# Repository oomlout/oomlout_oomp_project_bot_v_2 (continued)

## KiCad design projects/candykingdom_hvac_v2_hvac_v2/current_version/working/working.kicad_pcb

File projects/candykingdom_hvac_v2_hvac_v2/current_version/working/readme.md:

# hvac_v2
 
## summary 
* id: candykingdom_hvac_v2_hvac_v2
* user: candykingdom
* name: hvac_v2
* board: hvac_v2
* repo: https://github.com/candykingdom/hvac-v2
* src_file_repo_kicad_pcb: hardware/hvac-v2.kicad_pcb
* src_file_repo_kicad_pcb_link: https://github.com/candykingdom/hvac-v2/tree/master/hardware/hvac-v2.kicad_pcb
* src_file_repo_kicad_sch: hardware/hvac-v2.kicad_sch
* src_file_repo_kicad_sch_link: https://github.com/candykingdom/hvac-v2/tree/master/hardware/hvac-v2.kicad_sch

* src_file_repo_sch: hardware/hvac-v2.sch
* src_file_repo_sch_link: https://github.com/candykingdom/hvac-v2/tree/master/hardware/hvac-v2.sch
* full details link: https://github.com/oomlout/oomlout_oomp_project_bot_v_2/tree/main/projects/candykingdom_hvac_v2_hvac_v2/current_version/working

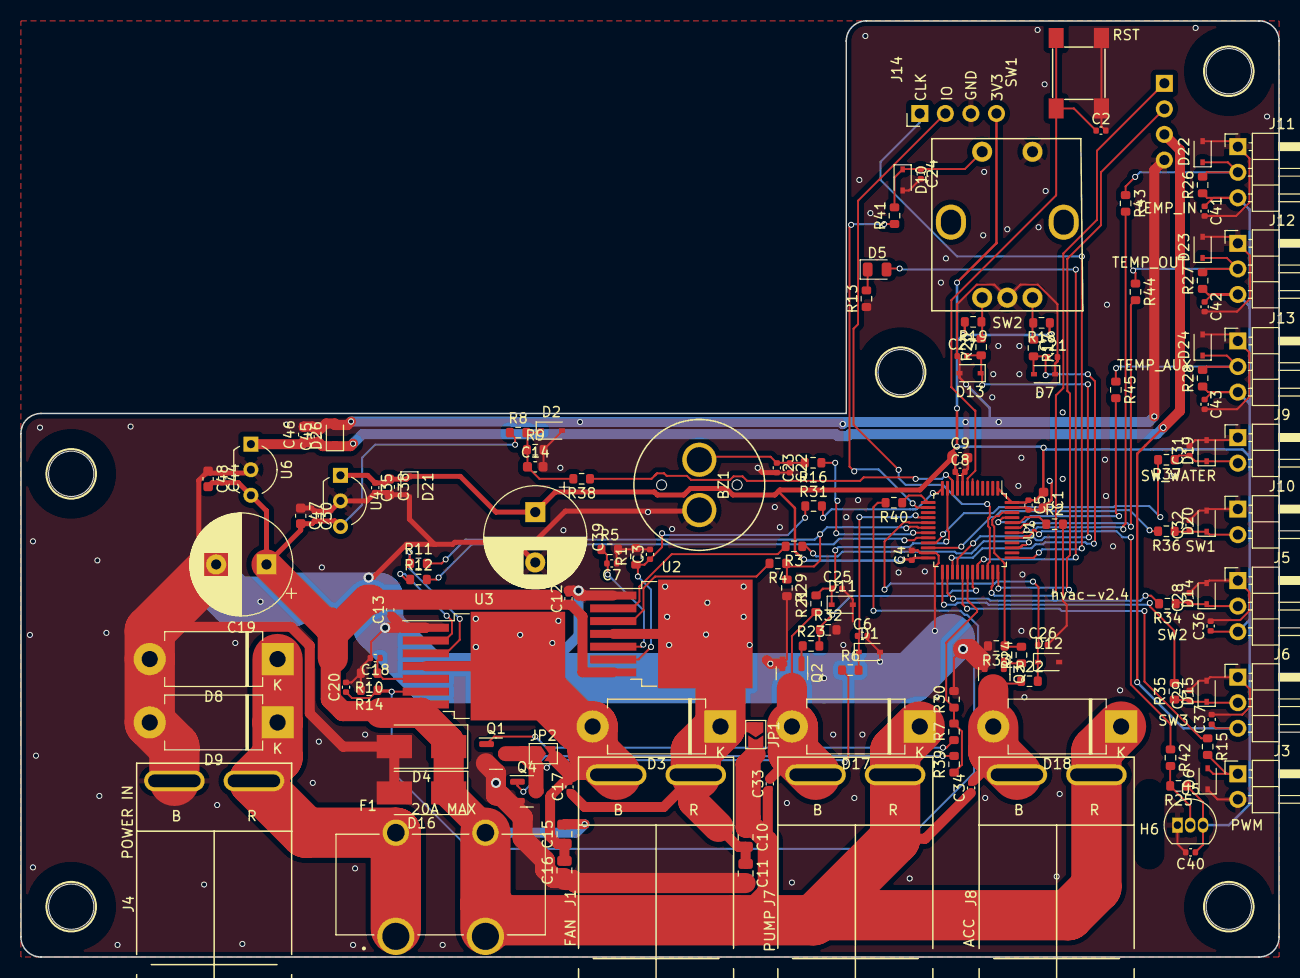
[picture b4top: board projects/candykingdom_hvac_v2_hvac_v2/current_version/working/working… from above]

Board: 2 copper layers, 125.0 x 93.0 mm, 154 parts (1 on the bottom side), 69 nets.

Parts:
BZ1: Buzzer; MURATA_PKM13EPYH4000-A0
C1, C9, C14, C38, C46, C47, C48: 4.7uF; C_0603_1608Metric
C2, C4, C5, C6, C7, C8, C12, C13, C17, C18, C22, C23, C24, C25, C26, C28, C29, C30, C31, C32, C33, C34, C35, C36, C37, C40, C41, C42, C43, C44, C45: 100nF; C_0402_1005Metric
C3, C20: 1nF; C_0402_1005Metric
C10, C11, C15, C16: 220nF; C_0805_2012Metric
C19: 1000uF; CP_Radial_D10.0mm_P5.00mm
C21, C27: 10nF; C_0402_1005Metric
C39: 470uF; CP_Radial_D10.0mm_P5.00mm
D1, D2, D6, D7, D10, D11, D12, D13, D14, D15, D19, D20, D21, D22, D23, D24, D26: TVS_5V; D_SOD-323
D3, D8, D9, D17, D18: D_Schottky; D_DO-201AD_P12.70mm_Horizontal
D4, D16: TVS_12V; D_SMB_Handsoldering
D5: LED; LED_0805_2012Metric
F1: ATC; FUSE_3550-2
H1, H2, H3, H4, H5: HOLE; HOLE_M4
H6: SLOT; SLOT_W2mm_H8mm
J1: Anderson_two_redblack; Anderson_1336G1_right_angle_bottom_two
J2, J14: Conn_01x04; PinHeader_1x04_P2.54mm_Horizontal
J3, J9, J10: Conn_01x02; PinHeader_1x02_P2.54mm_Horizontal
J4: Anderson_two_redblack_src; Anderson_1336G1_right_angle_bottom_two
J5, J6, J11, J12, J13: Conn_01x03; PinHeader_1x03_P2.54mm_Horizontal
J7, J8: Anderson_two_redblack_sink; Anderson_1336G1_right_angle_bottom_two
JP1, JP2: SolderJumper_2_Open; SolderJumper-2_P1.3mm_Open_TrianglePad1.0x1.5mm
Q1, Q2, Q3, Q4: AO3400A; SOT-23
R1, R14: 470; R_0603_1608Metric
R2, R6, R21, R22: 24k; R_0603_1608Metric
R3, R4, R5, R10, R11, R12, R17, R18, R19, R20, R30, R32, R33: 10k; R_0603_1608Metric
R7, R13, R15, R23, R24, R39, R42, R43, R44, R45: 150; R_0603_1608Metric
R8: 390k; R_0603_1608Metric
R9, R29: 110k; R_0603_1608Metric
R16: 47; R_0603_1608Metric
R25, R26, R27, R28: 4k7; R_0603_1608Metric
R31, R34, R35, R36, R37, R38, R40, R41: 1k; R_0603_1608Metric
SW1: SW_Push; SW_TACTILE_5.1MM_TS-1187A-C-D-B
SW2: Rotary_Encoder_Switch; BOURNS_PEC12R-4xxxF-Sxxxx
U1: STM32F030C8Tx; LQFP-48_7x7mm_P0.5mm
U2, U3: IFX007T; TO-263-7_TabPin8
U4, U6: AP7381-XXV; TO-92L_Inline_Wide
U5: DS18B20; TO-92_Inline

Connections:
+5V: C37.1, C45.1, C46.1, D26.1 (A1), J2.3, J6.3, U6.1 (VO)
+BATT: C10.1, C12.1, C13.2, C15.2, C19.1, C30.2, C33.1, C34.1, C44.2, C47.2, C48.2, D4.1 (A1), D16.1 (A1), D17.1 (K), D18.1 (K), F1.2 (OUT), J7.1, J8.1, JP1.2 (B), R8.1, U2.7 (VS), U3.7 (VS), U4.3 (VI), U6.3 (VI)
/ACC_OUT: C34.2, D18.2 (A), J8.2, Q3.3 (D), R22.1
/ACC_SENSE: C26.1, D12.1 (A1), R22.2, U1.17 (PA7)
/ACC_SIGNAL: R24.2, R33.1, U1.46 (PB9)
/BOOT0: R2.1, U1.44 (BOOT0)
/BRIDGE_ENABLE: R4.1, R11.2, R29.1, U1.18 (PB0)
/BRIDGE_N: R12.2, U1.20 (PB2)
/BRIDGE_P: R3.1, U1.39 (PB3)
/BRIDGE_SENSE_N: R40.1, U1.13 (PA3)
/BRIDGE_SENSE_P: R31.2, U1.12 (PA2)
/BUTTON: R41.1, U1.14 (PA4)
/BUZZER: R16.1, U1.19 (PB1)
/ENC_A: C21.1, D7.2 (A2), R17.2, U1.27 (PB14)
/ENC_B: C27.2, D13.1 (A1), R20.1, U1.28 (PB15)
/FAN_N: C15.1, C16.2, C17.2, D3.2 (A), J1.2, JP2.2 (B), U3.4 (OUT), U3.8 (OUT)
/FAN_P: C10.2, C11.1, C17.1, D3.1 (K), J1.1, JP1.1 (A), U2.4 (OUT), U2.8 (OUT)
/FAN_SENSE: C6.1, D1.1 (A1), R6.2, U1.16 (PA6)
/FAN_SIGNAL: R7.2, R30.1, R39.1, U1.30 (PA9)
/LED: D5.2 (A), U1.32 (PA11)
/NRST: C2.1, SW1.1, U1.7 (NRST)
/PUMP_OUT: C33.2, D17.2 (A), J7.2, Q2.3 (D), R21.1
/PUMP_SENSE: C25.1, D11.1 (A1), R21.2, U1.11 (PA1)
/PUMP_SIGNAL: R23.2, R32.1, U1.31 (PA10)
/PWM_OUT: R15.1, U1.29 (PA8)
/SCL: J2.1, U1.35 (PF6)
/SDA: J2.2, U1.36 (PF7)
/SWCLK: J14.1, U1.37 (PA14)
/SWDIO: J14.2, U1.34 (PA13)
/SW_1: R36.2, U1.22 (PB11)
/SW_2: R34.2, U1.26 (PB13)
/SW_3: R35.2, U1.25 (PB12)
/SW_WATER: R37.2, U1.21 (PB10)
/TEMP_AUX: R45.2, U1.45 (PB8)
/TEMP_BUILTIN: R42.1, U1.41 (PB5)
/TEMP_INSIDE: R43.2, U1.42 (PB6)
/TEMP_OUTSIDE: R44.2, U1.43 (PB7)
/VBATT_DIV: R38.1, U1.10 (PA0)
GND: BZ1.2 (+), C1.2, C2.2, C3.2, C4.2, C5.2, C6.2, C7.1, C8.2, C9.2, C11.2, C12.2, C13.1, C14.2, C16.1, C18.2, C19.2, C20.2, C21.2, C22.2, C23.2, C24.2, C25.2, C26.2, C27.1, C28.2, C29.2, C30.1, C31.2, C32.2, C35.2, C36.2, C37.2, C38.2, C39.2, C40.2, C41.2, C42.2, C43.2, C44.1, C45.2, C46.2, C47.1, C48.1, D1.2 (A2), D2.2 (A2), D4.2 (A2), D6.1 (A1), D7.1 (A1), D8.2 (A), D9.2 (A), D10.2 (A2), D11.2 (A2), D12.2 (A2), D13.2 (A2), D14.2 (A2), D15.2 (A2), D16.2 (A2), D19.2 (A2), D20.2 (A2), D21.2 (A2), D22.2 (A2), D23.2 (A2), D24.2 (A2), D26.2 (A2), J2.4, J3.2, J4.2, J5.1, J6.1, J9.1, J10.1, J11.1, J12.1, J13.1, J14.3, Q1.2 (S), Q2.2 (S), Q3.2 (S), Q4.2 (S), R1.2, R2.2, R5.2, R9.2, R10.2, R13.1, R14.2, R29.2, R30.2, R32.2, R33.2, SW1.2, SW2.C, SW2.S2, U1.8 (VSSA), U1.23 (VSS), U1.47 (VSS), U2.1 (GND), U3.1 (GND), U4.2 (GND), U5.1 (GND), U6.2 (GND)
unnamed: BZ1.1 (-), C22.1, C23.1, R16.2
unnamed: C3.1, R1.1, R31.1, U2.6 (IS)
unnamed: C7.2, R5.1, U2.5 (SR)
unnamed: C14.1, D2.1 (A1), R8.2, R9.1, R38.2
unnamed: C18.1, R10.1, U3.5 (SR)
unnamed: C20.1, R14.1, R40.2, U3.6 (IS)
unnamed: C24.1, D10.1 (A1), R41.2, SW2.S1
unnamed: C28.1, D14.1 (A1), J5.2, R34.1
unnamed: C29.1, D15.1 (A1), J6.2, R35.1
unnamed: C31.1, D19.1 (A1), J9.2, R37.1
unnamed: C32.1, D20.1 (A1), J10.2, R36.1
unnamed: D5.1 (K), R13.2
unnamed: D6.2 (A2), J3.1, R15.2
unnamed: D8.1 (K), D9.1 (K), F1.1 (IN), J4.1
unnamed: D22.1 (A1), J11.2, R26.2, R43.1
unnamed: D23.1 (A1), J12.2, R27.2, R44.1
unnamed: D24.1 (A1), J13.2, R28.2, R45.1
unnamed: JP2.1 (A), Q1.3 (D), Q4.3 (D), R6.1
unnamed: Q1.1 (G), R7.1
unnamed: Q2.1 (G), R23.1
unnamed: Q3.1 (G), R24.1
unnamed: Q4.1 (G), R39.2
unnamed: R3.2, U2.2 (IN)
unnamed: R4.2, U2.3 (INH)
unnamed: R11.1, U3.3 (INH)
unnamed: R12.1, U3.2 (IN)
unnamed: R17.1, R18.2, SW2.B
unnamed: R19.1, R20.2, SW2.A
unnamed: R25.2, R42.2, U5.2 (DQ)
VCC: C1.1, C4.1, C5.1, C8.1, C9.1, C35.1, C36.1, C38.1, C39.1, C40.1, C41.1, C42.1, C43.1, D21.1 (A1), J5.3, J11.3, J12.3, J13.3, J14.4, R18.1, R19.2, R25.1, R26.1, R27.1, R28.1, U1.1 (VDD), U1.9 (VDDA), U1.24 (VDD), U1.48 (VDD), U4.1 (VO), U5.3 (VDD)

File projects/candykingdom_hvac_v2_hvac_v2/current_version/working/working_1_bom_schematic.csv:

"Source:","C:\gh\oomlout_oomp_project_bot_v_2\projects\candykingdom_hvac_v2_hvac_v2\current_version\working\working_1.kicad_sch"
"Date:","27/09/2023 23:55:37"
"Tool:","Eeschema 7.0.6"
"Generator:","C:/Program Files/KiCad/7.0/bin/scripting/plugins/bom_csv_grouped_by_value_with_fp.py"
"Component Count:","154"
"Ref","Qnty","Value","Cmp name","Footprint","Description","Vendor","DNP"
"BZ1","1","Buzzer","Buzzer","Homebrew:MURATA_PKM13EPYH4000-A0","Buzzer, polarized","",""
"C1, C9, C14, C38, C46, C47, C48","7","4.7uF","C","Capacitor_SMD:C_0603_1608Metric","Unpolarized capacitor","",""
"C2, C4, C5, C6, C7, C8, C12, C13, C17, C18, C22, C23, C24, C25, C26, C28, C29, C30, C31, C32, C33, C34, C35, C36, C37, C40, C41, C42, C43, C44, C45","31","100nF","C","Capacitor_SMD:C_0402_1005Metric","Unpolarized capacitor","",""
"C3, C20","2","1nF","C","Capacitor_SMD:C_0402_1005Metric","Unpolarized capacitor","",""
"C10, C11, C15, C16","4","220nF","C","Capacitor_SMD:C_0805_2012Metric","Unpolarized capacitor","",""
"C19","1","1000uF","C_Polarized","Capacitor_THT:CP_Radial_D10.0mm_P5.00mm","Polarized capacitor","",""
"C21, C27","2","10nF","C","Capacitor_SMD:C_0402_1005Metric","Unpolarized capacitor","",""
"C39","1","470uF","C_Polarized","Capacitor_THT:CP_Radial_D10.0mm_P5.00mm","Polarized capacitor","",""
"D1, D2, D6, D7, D10, D11, D12, D13, D14, D15, D19, D20, D21, D22, D23, D24, D26","17","TVS_5V","D_TVS","Diode_SMD:D_SOD-323","Bidirectional transient-voltage-suppression diode","",""
"D3, D8, D9, D17, D18","5","D_Schottky","D_Schottky","Diode_THT:D_DO-201AD_P12.70mm_Horizontal","Schottky diode","",""
"D4, D16","2","TVS_12V","D_TVS","Diode_SMD:D_SMB_Handsoldering","Bidirectional transient-voltage-suppression diode","",""
"D5","1","LED","LED","LED_SMD:LED_0805_2012Metric","Light emitting diode","",""
"F1","1","ATC","POWER_FUSE","Homebrew:FUSE_3550-2","","",""
"H1, H2, H3, H4, H5","5","HOLE","HOLE","Homebrew:HOLE_M4","","",""
"H6","1","SLOT","HOLE","Homebrew:SLOT_W2mm_H8mm","","",""
"J1","1","Anderson_two_redblack","Anderson_two_redblack","Homebrew:Anderson_1336G1_right_angle_bottom_two","","",""
"J2, J14","2","Conn_01x04","Conn_01x04","Connector_PinHeader_2.54mm:PinHeader_1x04_P2.54mm_Horizontal","Generic connector, single row, 01x04, script generated (kicad-library-utils/schlib/autogen/connector/)","",""
"J3, J9, J10","3","Conn_01x02","Conn_01x02","Connector_PinHeader_2.54mm:PinHeader_1x02_P2.54mm_Horizontal","Generic connector, single row, 01x02, script generated (kicad-library-utils/schlib/autogen/connector/)","",""
"J4","1","Anderson_two_redblack_src","Anderson_two_redblack_src","Homebrew:Anderson_1336G1_right_angle_bottom_two","","",""
"J5, J6, J11, J12, J13","5","Conn_01x03","Conn_01x03","Connector_PinHeader_2.54mm:PinHeader_1x03_P2.54mm_Horizontal","Generic connector, single row, 01x03, script generated (kicad-library-utils/schlib/autogen/connector/)","",""
"J7, J8","2","Anderson_two_redblack_sink","Anderson_two_redblack_sink","Homebrew:Anderson_1336G1_right_angle_bottom_two","","",""
"JP1, JP2","2","SolderJumper_2_Open","SolderJumper_2_Open","Jumper:SolderJumper-2_P1.3mm_Open_TrianglePad1.0x1.5mm","Solder Jumper, 2-pole, open","",""
"Q1, Q2, Q3, Q4","4","AO3400A","AO3400A","Package_TO_SOT_SMD:SOT-23","30V Vds, 5.7A Id, N-Channel MOSFET, SOT-23","",""
"R1, R14","2","470","R","Resistor_SMD:R_0603_1608Metric","Resistor","",""
"R2, R6, R21, R22","4","24k","R","Resistor_SMD:R_0603_1608Metric","Resistor","",""
"R3, R4, R5, R10, R11, R12, R17, R18, R19, R20, R30, R32, R33","13","10k","R","Resistor_SMD:R_0603_1608Metric","Resistor","",""
"R7, R13, R15, R23, R24, R39, R42, R43, R44, R45","10","150","R","Resistor_SMD:R_0603_1608Metric","Resistor","",""
"R8","1","390k","R","Resistor_SMD:R_0603_1608Metric","Resistor","",""
"R9, R29","2","110k","R","Resistor_SMD:R_0603_1608Metric","Resistor","",""
"R16","1","47","R","Resistor_SMD:R_0603_1608Metric","Resistor","",""
"R25, R26, R27, R28","4","4k7","R","Resistor_SMD:R_0603_1608Metric","Resistor","",""
"R31, R34, R35, R36, R37, R38, R40, R41","8","1k","R","Resistor_SMD:R_0603_1608Metric","Resistor","",""
"SW1","1","SW_Push","SW_Push","Homebrew:SW_TACTILE_5.1MM_TS-1187A-C-D-B","Push button switch, generic, two pins","",""
"SW2","1","Rotary_Encoder_Switch","RotaryEncoder_Switch","Homebrew:BOURNS_PEC12R-4xxxF-Sxxxx","Rotary encoder, dual channel, incremental quadrate outputs, with switch","",""
"U1","1","STM32F030C8Tx","STM32F030C8Tx","Package_QFP:LQFP-48_7x7mm_P0.5mm","ARM Cortex-M0 MCU, 64KB flash, 8KB RAM, 48MHz, 2.4-3.6V, 39 GPIO, LQFP-48","",""
"U2, U3","2","IFX007T","IFX007T","Package_TO_SOT_SMD:TO-263-7_TabPin8","","",""
"U4, U6","2","AP7381-XXV","AP7381-XXV","Package_TO_SOT_THT:TO-92L_Inline_Wide","150mA Low Dropout Voltage Regulator, Fixed Output, TO-92","",""
"U5","1","DS18B20","DS18B20","Package_TO_SOT_THT:TO-92_Inline","Programmable Resolution 1-Wire Digital Thermometer TO-92","",""

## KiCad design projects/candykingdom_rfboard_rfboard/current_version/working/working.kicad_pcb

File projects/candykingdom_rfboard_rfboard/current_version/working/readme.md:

# rfboard
 
## summary 
* id: candykingdom_rfboard_rfboard
* user: candykingdom
* name: rfboard
* board: rfboard
* repo: https://github.com/candykingdom/rfboard
* src_file_repo_kicad_pcb: hardware/rfboard.kicad_pcb
* src_file_repo_kicad_pcb_link: https://github.com/candykingdom/rfboard/tree/master/hardware/rfboard.kicad_pcb

* src_file_repo_sch: hardware/rfboard.sch
* src_file_repo_sch_link: https://github.com/candykingdom/rfboard/tree/master/hardware/rfboard.sch
* full details link: https://github.com/oomlout/oomlout_oomp_project_bot_v_2/tree/main/projects/candykingdom_rfboard_rfboard/current_version/working

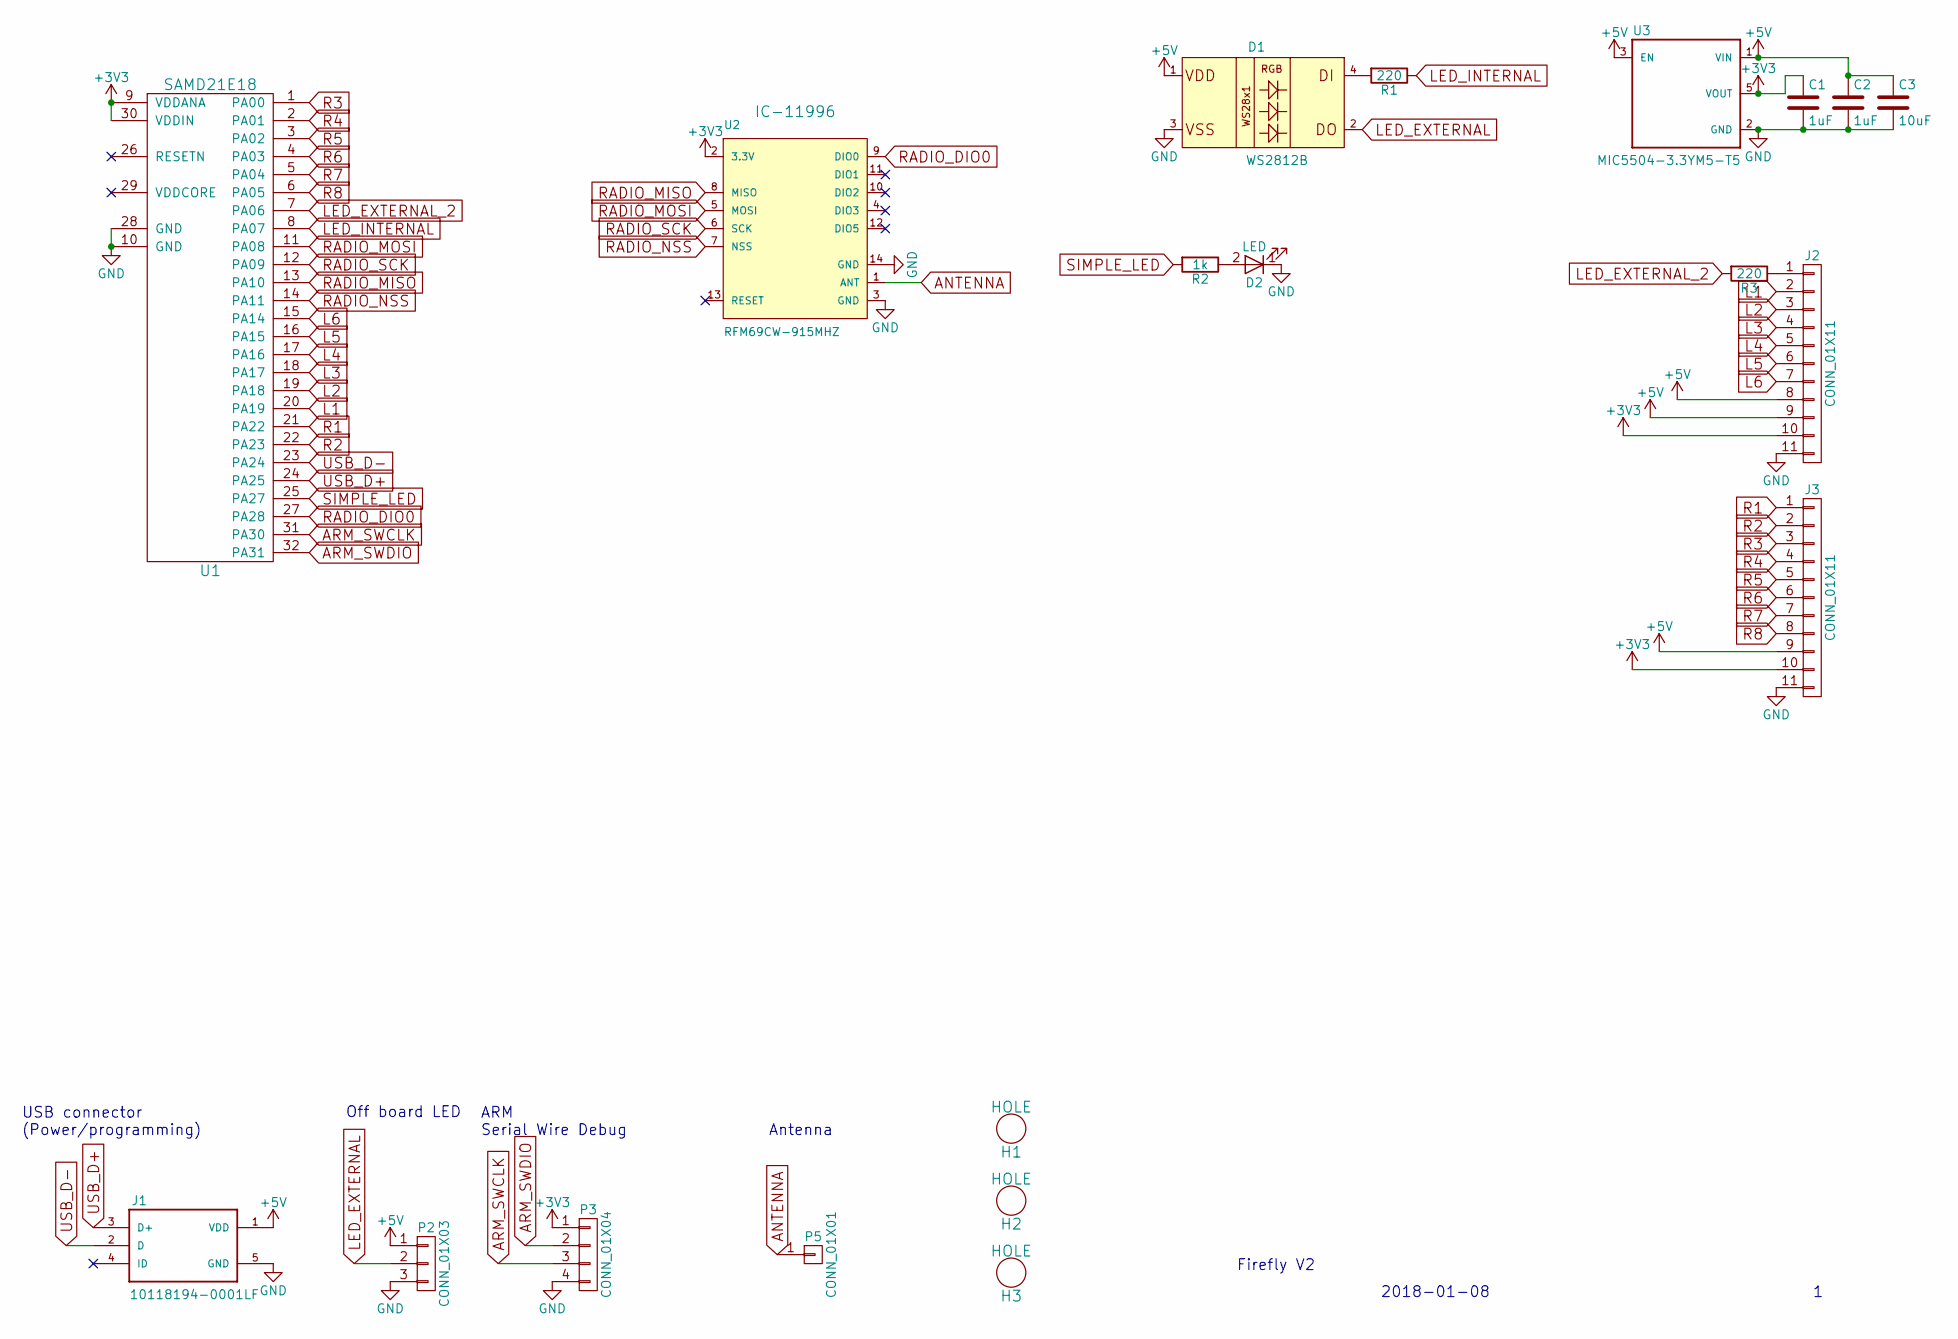
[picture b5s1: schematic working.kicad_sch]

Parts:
C1, C2: 1uF; C_0603_HandSoldering
C3: 10uF; C_0805_HandSoldering
D1: WS2812B
D2: LED; LED_0603
H1, H2, H3: HOLE; MountingHole_2.7mm_M2.5
J1: 10118194-0001LF; FRAMATOME_10118194-0001LF
J2, J3: CONN_01X11; Pin_Header_Straight_1x11_Pitch2.54mm
P2: CONN_01X03; 1X03
P3: CONN_01X04; 1X04
P5: CONN_01X01; 1X01
R1, R3: 220; R_0603_HandSoldering
R2: 1k; R_0603_HandSoldering
U1: SAMD21E18; TQFP32-08
U2: RFM69CW-915MHZ; RFM69CW-XXXS2_
U3: MIC5504-3.3YM5-T5; SOT23-5P95_280X145XL45X37N

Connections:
+3V3: C1.1, J2.10, J3.10, P3.1, U1.9 (VDDANA), U1.30 (VDDIN), U2.2 (3.3V), U3.5 (VOUT)
+5V: C2.1, C3.1, D1.1 (VDD), J1.1 (VDD), J2.8, J2.9, J3.9, P2.1, U3.1 (VIN), U3.3 (EN)
ANTENNA: P5.1, U2.1 (ANT)
ARM_SWCLK: P3.3, U1.31 (PA30)
ARM_SWDIO: P3.2, U1.32 (PA31)
GND: C1.2, C2.2, C3.2, D1.3 (VSS), D2.1 (K), J1.5 (GND), J2.11, J3.11, P2.3, P3.4, U1.10 (GND), U1.28 (GND), U2.3 (GND), U2.14 (GND), U3.2 (GND)
L1: J2.2, U1.20 (PA19)
L2: J2.3, U1.19 (PA18)
L3: J2.4, U1.18 (PA17)
L4: J2.5, U1.17 (PA16)
L5: J2.6, U1.16 (PA15)
L6: J2.7, U1.15 (PA14)
LED_EXTERNAL: D1.2 (DO), P2.2
LED_EXTERNAL_2: R3.2, U1.7 (PA06)
LED_INTERNAL: R1.1, U1.8 (PA07)
unnamed: D1.4 (DI), R1.2
unnamed: D2.2 (A), R2.1
unnamed: J2.1, R3.1
R1: J3.1, U1.21 (PA22)
R2: J3.2, U1.22 (PA23)
R3: J3.3, U1.1 (PA00)
R4: J3.4, U1.2 (PA01)
R5: J3.5, U1.3 (PA02)
R6: J3.6, U1.4 (PA03)
R7: J3.7, U1.5 (PA04)
R8: J3.8, U1.6 (PA05)
RADIO_DIO0: U1.27 (PA28), U2.9 (DIO0)
RADIO_MISO: U1.13 (PA10), U2.8 (MISO)
RADIO_MOSI: U1.11 (PA08), U2.5 (MOSI)
RADIO_NSS: U1.14 (PA11), U2.7 (NSS)
RADIO_SCK: U1.12 (PA09), U2.6 (SCK)
SIMPLE_LED: R2.2, U1.25 (PA27)
USB_D+: J1.3 (D+), U1.24 (PA25)
USB_D-: J1.2 (D), U1.23 (PA24)

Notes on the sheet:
USB connector (Power/programming)
Antenna
2018-01-08
Firefly V2
ARM Serial Wire Debug
Off board LED

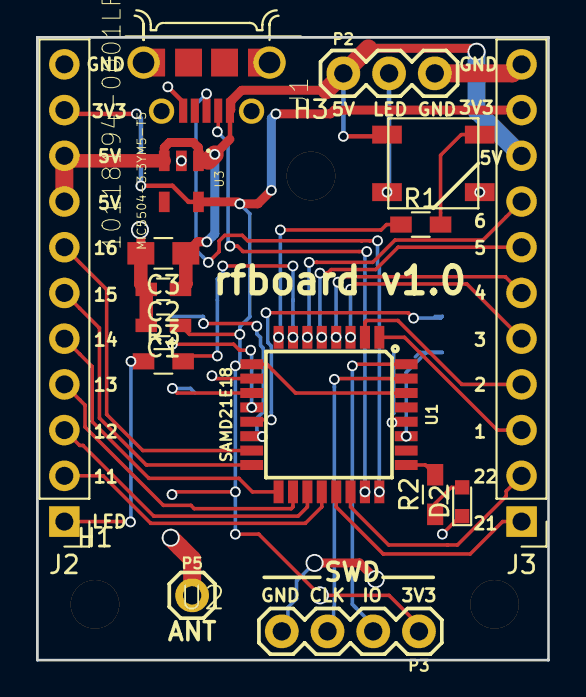
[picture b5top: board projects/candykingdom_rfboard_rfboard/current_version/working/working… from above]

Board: 2 copper layers, 28.4 x 34.6 mm, 20 parts (1 on the bottom side), 34 nets.

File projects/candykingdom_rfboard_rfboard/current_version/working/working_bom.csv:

"Id";"Designator";"Footprint";"Quantity";"Designation";"Supplier and ref";
1;"C1,C2";"C_0603_HandSoldering";2;"1uF";;;
2;"C3";"C_0805_HandSoldering";1;"10uF";;;
3;"D1";"WS2812B";1;"WS2812B";;;
4;"D2";"LED_0603";1;"LED";;;
5;"J1";"FRAMATOME_10118194-0001LF";1;"10118194-0001LF";;;
6;"J2,J3";"Pin_Header_Straight_1x11_Pitch2.54mm";2;"CONN_01X11";;;
7;"R1,R3";"R_0603_HandSoldering";2;"220";;;
8;"R2";"R_0603_HandSoldering";1;"1k";;;
9;"U1";"TQFP32-08";1;"SAMD21E18";;;
10;"U3";"SOT23-5P95_280X145XL45X37N";1;"MIC5504-3.3YM5-T5";;;
11;"H1,H2,H3";"MountingHole_2.7mm_M2.5";3;"HOLE";;;
12;"U2";"RFM69CW-XXXS2_";1;"RFM69CW-915MHZ";;;

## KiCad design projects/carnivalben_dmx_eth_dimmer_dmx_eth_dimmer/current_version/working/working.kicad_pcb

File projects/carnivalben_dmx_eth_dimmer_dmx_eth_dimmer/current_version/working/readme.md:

# dmx_eth_dimmer
 
## summary 
* id: carnivalben_dmx_eth_dimmer_dmx_eth_dimmer
* user: carnivalben
* name: dmx_eth_dimmer
* board: dmx_eth_dimmer
* repo: https://github.com/CarnivalBen/dmx-eth-dimmer
* src_file_repo_kicad_pcb: pcb/dmx-eth-dimmer-prototype.kicad_pcb
* src_file_repo_kicad_pcb_link: https://github.com/CarnivalBen/dmx-eth-dimmer/tree/master/pcb/dmx-eth-dimmer-prototype.kicad_pcb

* src_file_repo_sch: 
* src_file_repo_sch_link: https://github.com/CarnivalBen/dmx-eth-dimmer/tree/master/
* full details link: https://github.com/oomlout/oomlout_oomp_project_bot_v_2/tree/main/projects/carnivalben_dmx_eth_dimmer_dmx_eth_dimmer/current_version/working  

## pcb  

[board (pdf)](working.pdf)  

## working_bom
| Id | Designator | Footprint | Quantity | Designation | Supplier and ref |  | None | 
| --- | --- | --- | --- | --- | --- | --- | --- | 
| 1 | C1,C2 | C_Disc_D3.0mm_W1.6mm_P2.50mm | 2 | 33pF |  |  | [''] | 
| 2 | C3 | CP_Radial_D10.0mm_P5.00mm | 1 | 1000uF |  |  | [''] | 
| 3 | C5,C6,C7,C8,C9,C10,C11,C12,C13 | C_Disc_D3.0mm_W1.6mm_P2.50mm | 9 | 0.01uF |  |  | [''] | 
| 4 | D1 | LED_D3.0mm | 1 | CFG Status |  |  | [''] | 
| 5 | D2 | LED_D3.0mm | 1 | Ethernet Status |  |  | [''] | 
| 6 | D4,D5,D6,D7,D8,D9,D10,D11 | TO-220-3_Vertical | 8 | BTA08-600 |  |  | [''] | 
| 7 | J1 | TerminalBlock_bornier-2_P5.08mm | 1 | MAINS IN |  |  | [''] | 
| 8 | J2 | Pin_Header_Straight_2x06_Pitch2.54mm | 1 | STANDARD ENC28J60 |  |  | [''] | 
| 9 | J3 | Pin_Header_Straight_2x05_Pitch2.54mm | 1 | MINI ENC28J60 |  |  | [''] | 
| 10 | J4 | Pin_Header_Straight_1x06_Pitch2.54mm | 1 | MASTER PROG |  |  | [''] | 
| 11 | J5,J7,J9,J11,J13,J15,J17,J19 | Pin_Header_Straight_1x06_Pitch2.54mm | 8 | PRG |  |  | [''] | 
| 12 | J6,J8,J10,J12,J14,J16,J18,J20 | TerminalBlock_bornier-2_P5.08mm | 8 | LOAD |  |  | [''] | 
| 13 | SW7 | SW_DIP_x8_W7.62mm_Slide | 1 | SW_DIP_x08 |  |  | [''] | 
| 14 | U2 | TO-220-3_Vertical | 1 | 3.3v Regulator |  |  | [''] | 
| 15 | U3 | DIP-14_W7.62mm | 1 | 74HCT08 |  |  | [''] | 
| 16 | U4 | DIP-6_W7.62mm | 1 | 4N25 |  |  | [''] | 
| 17 | U5,U7,U9,U11,U13,U15,U17,U19 | DIP-8_W7.62mm | 8 | PIC12(L)F1571/2 |  |  | [''] | 
| 18 | U6,U8,U10,U12,U14,U16,U18,U20 | DIP-6_W7.62mm | 8 | MOC3020M |  |  | [''] | 
| 19 | Y1 | Crystal_HC50_Vertical | 1 | 20MHz |  |  | [''] | 
| 20 | F1 | Fuseholder5x20_horiz_open_inline_Type-I | 1 | 100mA |  |  | [''] | 
| 21 | F2,F3,F4,F5,F6,F7,F8,F9 | Fuseholder5x20_horiz_open_inline_Type-I | 8 | 5A |  |  | [''] | 
| 22 | R16,R18,R20,R22,R24,R26,R12,R14 | R_Axial_DIN0207_L6.3mm_D2.5mm_P10.16mm_Horizontal | 8 | 240 |  |  | [''] | 
| 23 | R17,R19,R21,R23,R25,R27,R13,R15 | R_Axial_DIN0207_L6.3mm_D2.5mm_P10.16mm_Horizontal | 8 | 180 |  |  | [''] | 
| 24 | R1,R2,R3,R8,R9,R10,R11,R30 | R_Axial_DIN0207_L6.3mm_D2.5mm_P10.16mm_Horizontal | 8 | 10K |  |  | [''] | 
| 25 | R4,R5,R6,R7 | R_Axial_DIN0207_L6.3mm_D2.5mm_P10.16mm_Horizontal | 4 | 300 |  |  | [''] | 
| 26 | R28 | R_Axial_DIN0207_L6.3mm_D2.5mm_P10.16mm_Horizontal | 1 | 100K |  |  | [''] | 
| 27 | R29 | R_Axial_DIN0207_L6.3mm_D2.5mm_P10.16mm_Horizontal | 1 | 120 |  |  | [''] | 
| 28 | D3 | Diode_Bridge_W08 | 1 | BRIDGE |  |  | [''] | 
| 29 | SW1 | SW_PUSH_6mm_4pin | 1 | IP1 |  |  | [''] | 
| 30 | SW2 | SW_PUSH_6mm_4pin | 1 | IP2 |  |  | [''] | 
| 31 | SW3 | SW_PUSH_6mm_4pin | 1 | IP3 |  |  | [''] | 
| 32 | SW4 | SW_PUSH_6mm_4pin | 1 | IP4 |  |  | [''] | 
| 33 | SW5 | SW_PUSH_6mm_4pin | 1 | DMXAH |  |  | [''] | 
| 34 | SW6 | SW_PUSH_6mm_4pin | 1 | DMXAL |  |  | [''] | 
| 35 | U***1 | DIP-40_W15.24mm | 1 | PIC16F877A |  |  | [''] | 
| 36 | U1 | HLK-PM01 | 1 | PSU-5VDC |  |  | [''] |

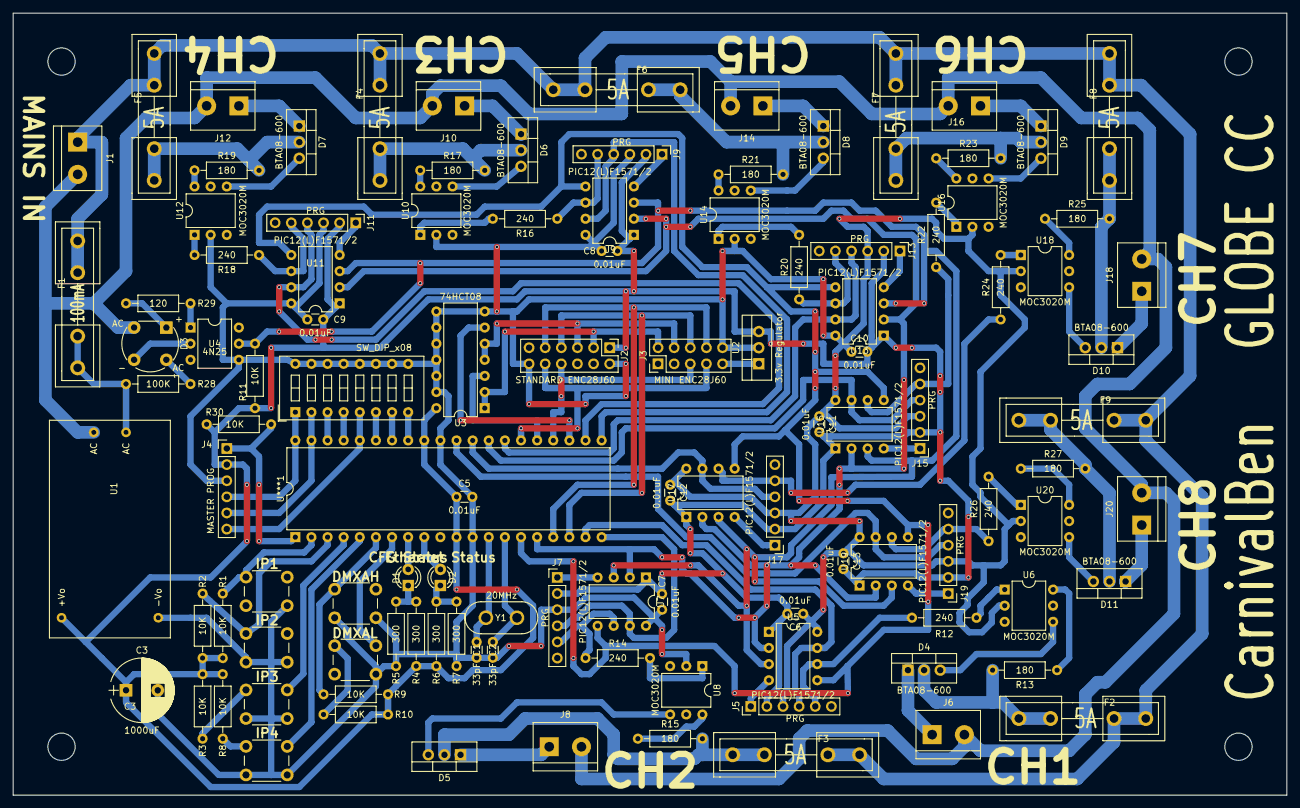
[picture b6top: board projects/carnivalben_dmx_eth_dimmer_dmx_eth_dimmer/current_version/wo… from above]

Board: 2 copper layers, 200.7 x 123.2 mm, 111 parts (0 on the bottom side), 109 nets.

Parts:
C1, C2: 33pF; C_Disc_D3.0mm_W1.6mm_P2.50mm
C3: 1000uF; CP_Radial_D10.0mm_P5.00mm
C5, C6, C7, C8, C9, C10, C11, C12, C13: 0.01uF; C_Disc_D3.0mm_W1.6mm_P2.50mm
D1: CFG Status; LED_D3.0mm
D2: Ethernet Status; LED_D3.0mm
D3: BRIDGE; Diode_Bridge_W08
D4, D5, D6, D7, D8, D9, D10, D11: BTA08-600; TO-220-3_Vertical
F1: 100mA; Fuseholder5x20_horiz_open_inline_Type-I
F2, F3, F4, F5, F6, F7, F8, F9: 5A; Fuseholder5x20_horiz_open_inline_Type-I
J1: MAINS IN; TerminalBlock_bornier-2_P5.08mm
J2: STANDARD ENC28J60; Pin_Header_Straight_2x06_Pitch2.54mm
J3: MINI ENC28J60; Pin_Header_Straight_2x05_Pitch2.54mm
J4: MASTER PROG; Pin_Header_Straight_1x06_Pitch2.54mm
J5, J7, J9, J11, J13, J15, J17, J19: PRG; Pin_Header_Straight_1x06_Pitch2.54mm
J6, J8, J10, J12, J14, J16, J18, J20: LOAD; TerminalBlock_bornier-2_P5.08mm
R1, R2, R3, R8, R9, R10, R11, R30: 10K; R_Axial_DIN0207_L6.3mm_D2.5mm_P10.16mm_Horizontal
R4, R5, R6, R7: 300; R_Axial_DIN0207_L6.3mm_D2.5mm_P10.16mm_Horizontal
R12, R14, R16, R18, R20, R22, R24, R26: 240; R_Axial_DIN0207_L6.3mm_D2.5mm_P10.16mm_Horizontal
R13, R15, R17, R19, R21, R23, R25, R27: 180; R_Axial_DIN0207_L6.3mm_D2.5mm_P10.16mm_Horizontal
R28: 100K; R_Axial_DIN0207_L6.3mm_D2.5mm_P10.16mm_Horizontal
R29: 120; R_Axial_DIN0207_L6.3mm_D2.5mm_P10.16mm_Horizontal
SW1: IP1; SW_PUSH_6mm_4pin
SW2: IP2; SW_PUSH_6mm_4pin
SW3: IP3; SW_PUSH_6mm_4pin
SW4: IP4; SW_PUSH_6mm_4pin
SW5: DMXAH; SW_PUSH_6mm_4pin
SW6: DMXAL; SW_PUSH_6mm_4pin
SW7: SW_DIP_x08; SW_DIP_x8_W7.62mm_Slide
U1: PSU-5VDC; HLK-PM01
U2: 3.3v Regulator; TO-220-3_Vertical
U3: 74HCT08; DIP-14_W7.62mm
U4: 4N25; DIP-6_W7.62mm
U5, U7, U9, U11, U13, U15, U17, U19: PIC12(L)F1571/2; DIP-8_W7.62mm
U6, U8, U10, U12, U14, U16, U18, U20: MOC3020M; DIP-6_W7.62mm
U***1: PIC16F877A; DIP-40_W15.24mm
Y1: 20MHz; Crystal_HC50_Vertical

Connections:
5V: C3.1, C5.1, C6.2, C7.2, C8.2, C9.2, C10.2, C11.2, C12.2, C13.2, J2.1, J4.2, J5.2, J7.2, J9.2, J11.2, J13.2, J15.2, J17.2, J19.2, R1.2, R2.2, R3.2, R4.1, R6.1, R8.2, R9.2, R10.2, R11.1, R30.2, U1.1, U2.3, U3.14, U5.1, U7.1, U9.1, U11.1, U13.1, U15.1, U17.1, U19.1, U***1.11, U***1.32
/BIT0: SW7.8, U***1.33
/BIT1: SW7.7, U***1.34
/BIT2: SW7.6, U***1.35
/BIT3: J4.6, SW7.5, U***1.36
/BIT4: SW7.4, U***1.37
/BIT5: SW7.3, U***1.38
/BIT6: J4.5, SW7.2, U***1.39
/BIT7: J4.4, SW7.1, U***1.40
/CH1: J5.4, U5.7, U***1.19
/CH2: J7.4, U7.7, U***1.20
/CH3: J9.4, U9.7, U***1.21
/CH4: J11.4, U11.7, U***1.22
/CH5: J13.4, U13.7, U***1.27
/CH6: J15.4, U15.7, U***1.28
/CH7: J17.4, U17.7, U***1.29
/CH8: J19.4, U19.7, U***1.30
/CS: J2.10, J3.7, U***1.26
/Channel 1/GATE: D4.3, U6.4
/Channel 1/MT1: D4.1, J6.1
/Channel 1/MT2: D4.2, F2.2, R13.2
/Channel 2/GATE: D5.3, U8.4
/Channel 2/MT1: D5.1, J8.1
/Channel 2/MT2: D5.2, F3.2, R15.2
/Channel 3/GATE: D6.3, U10.4
/Channel 3/MT1: D6.1, J10.1
/Channel 3/MT2: D6.2, F4.2, R17.2
/Channel 4/GATE: D7.3, U12.4
/Channel 4/MT1: D7.1, J12.1
/Channel 4/MT2: D7.2, F5.2, R19.2
/Channel 5/GATE: D8.3, U14.4
/Channel 5/MT1: D8.1, J14.1
/Channel 5/MT2: D8.2, F6.2, R21.2
/Channel 6/GATE: D9.3, U16.4
/Channel 6/MT1: D9.1, J16.1
/Channel 6/MT2: D9.2, F7.2, R23.2
/Channel 7/GATE: D10.3, U18.4
/Channel 7/MT1: D10.1, J18.1
/Channel 7/MT2: D10.2, F8.2, R25.2
/Channel 8/GATE: D11.3, U20.4
/Channel 8/MT1: D11.1, J20.1
/Channel 8/MT2: D11.2, F9.2, R27.2
/DATACLK: J2.7, J3.6, U***1.18
/DMXAH: R9.1, SW5.4, U***1.6
/DMXAL: SW6.2, U***1.7
/FUSED_LIVE: F1.1, R28.2, U1.3
/INT: J2.3, J3.2, U3.1, U3.2
/INT5v: U3.3, U***1.25
/IP1: R1.1, SW1.4, U***1.2
/IP2: R2.1, SW2.4, U***1.3
/IP3: SW3.2, U***1.4
/IP4: SW4.2, U***1.5
/MCLR: J4.1, R30.1, U***1.1
/OSC1: C1.1, U***1.13, Y1.2
/OSC2: C2.1, U***1.14, Y1.1
/RESET: J2.9, J3.8, U***1.17
/RX: J2.5, J3.4, U3.4, U3.5
/RX5v: U3.6, U***1.23
/TX: J2.8, J3.5, U***1.24
/ZC_RETURN: D3.2, U4.2
/ZC_SIG: D3.3, R28.1
CFG_STATUS: D1.2, U***1.8
CHNCLK: U5.5, U7.5, U9.5, U11.5, U13.5, U15.5, U17.5, U19.5, U***1.15
CHNDATA: U5.2, U7.2, U9.2, U11.2, U13.2, U15.2, U17.2, U19.2, U***1.16
ETH_STATUS: D2.2, U***1.9
GND: C1.2, C2.2, C3.2, C5.2, C6.1, C7.1, C8.1, C9.1, C10.1, C11.1, C12.1, C13.1, J2.2, J2.12, J3.10, J4.3, J5.3, J7.3, J9.3, J11.3, J13.3, J15.3, J17.3, J19.3, R5.1, R7.1, SW1.1, SW2.1, SW2.3, SW3.1, SW3.3, SW4.1, SW4.3, SW5.1, SW5.3, SW6.1, SW7.9, SW7.10, SW7.11, SW7.12, SW7.13, SW7.14, SW7.15, SW7.16, U1.2, U2.2, U3.7, U3.8, U3.9, U3.10, U3.11, U3.12, U3.13, U4.4, U5.8, U6.2, U7.8, U8.2, U9.8, U10.2, U11.8, U12.2, U13.8, U14.2, U15.8, U16.2, U17.8, U18.2, U19.8, U20.2, U***1.12, U***1.31
LIVE: F1.2, F2.1, F3.1, F4.1, F5.1, F6.1, F7.1, F8.1, F9.1, J1.1
NEUTRAL: D3.4, J1.2, J6.2, J8.2, J10.2, J12.2, J14.2, J16.2, J18.2, J20.2, U1.4
unnamed: D1.1, R4.2, R5.2
unnamed: D2.1, R6.2, R7.2
unnamed: D3.1, R29.2
unnamed: J3.9, U2.1
unnamed: J5.1, U5.4
unnamed: J5.5, R12.1, U5.6
unnamed: J7.1, U7.4
unnamed: J7.5, R14.1, U7.6
unnamed: J9.1, U9.4
unnamed: J9.5, R16.1, U9.6
unnamed: J11.1, U11.4
unnamed: J11.5, R18.1, U11.6
unnamed: J13.1, U13.4
unnamed: J13.5, R20.1, U13.6
unnamed: J15.1, U15.4
unnamed: J15.5, R22.1, U15.6
unnamed: J17.1, U17.4
unnamed: J17.5, R24.1, U17.6
unnamed: J19.1, U19.4
unnamed: J19.5, R26.1, U19.6
unnamed: R3.1, SW3.4
unnamed: R8.1, SW4.4
unnamed: R10.1, SW6.4
unnamed: R12.2, U6.1
unnamed: R13.1, U6.6
unnamed: R14.2, U8.1
unnamed: R15.1, U8.6
unnamed: R16.2, U10.1
unnamed: R17.1, U10.6
unnamed: R18.2, U12.1
unnamed: R19.1, U12.6
unnamed: R20.2, U14.1
unnamed: R21.1, U14.6
unnamed: R22.2, U16.1
unnamed: R23.1, U16.6
unnamed: R24.2, U18.1
unnamed: R25.1, U18.6
unnamed: R26.2, U20.1
unnamed: R27.1, U20.6
unnamed: R29.1, U4.1
ZC: R11.2, U4.5, U5.3, U7.3, U9.3, U11.3, U13.3, U15.3, U17.3, U19.3
